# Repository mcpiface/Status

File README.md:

# McPiFace Status Board

Rack Mountable Raspberry Pi Status Board.

A status board in the McPiFace series, intended to fit the 19" rack frame as a quick status indicator.

Based on the Status Board Hat: https://thepihut.com/products/status-board-pro

## Versions

Version 2: Uses MCP23017 with The Pi's I2C. Uses the McPi I2C 6 Pin JST SH connection
https://github.com/mcpiface/Status/tree/master/V2

Version 1: Needs 3x connectors and 15 GPIO on Pi. Uses Pi GPIOs - similar (different pins) to the Status Board Hat.
https://github.com/mcpiface/Status/tree/master/V1

## Sled

To mount the raspberry Pi a 3D printable sled is available:

https://www.thingiverse.com/thing:3488157

## Rack Mount Frame

DAP Audio 2 HE Rackblende f. Modulsystem 10 Segmente MP-1 from Music Store.

* UK: https://www.dv247.com/en_GB/GBP/DAP-Audio-2-HE-Rackblende-f-Modulsystem-10-Segmente-MP-1/art-PAH0017160-000

* Germany: https://www.musicstore.de/en_US/USD/DAP-Audio-2-HE-Rackblende-f-Modulsystem-10-Segmente-MP-1/art-PAH0017160-000

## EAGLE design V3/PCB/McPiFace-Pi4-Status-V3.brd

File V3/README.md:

# McPiFace Status Board - Version 2

Rack Mountable Raspberry Pi Status Board.

Features 4x status indicators with red/green LEDs and optional buttons.

A status board in the McPiFace series, intended to fit the 19" rack frame as a quick status indicator.

This version uses the MCP23017 with The Pi's I2C. 

The connection uses the McPi I2C 6 Pin JST SH connection (1:1 connection with the first 6 pins of the Raspberry Pi second row of pins on the 40 pin header).

![Schematic] (Images/Schematic.png)

## Examples

See the examples folder for examples of use.

## Sled

To mount the raspberry Pi a 3D printable sled is available:

https://www.thingiverse.com/thing:3488157

## Rack Mount Frame

DAP Audio 2 HE Rackblende f. Modulsystem 10 Segmente MP-1 from Music Store.

* UK: https://www.dv247.com/en_GB/GBP/DAP-Audio-2-HE-Rackblende-f-Modulsystem-10-Segmente-MP-1/art-PAH0017160-000

* Germany: https://www.musicstore.de/en_US/USD/DAP-Audio-2-HE-Rackblende-f-Modulsystem-10-Segmente-MP-1/art-PAH0017160-000

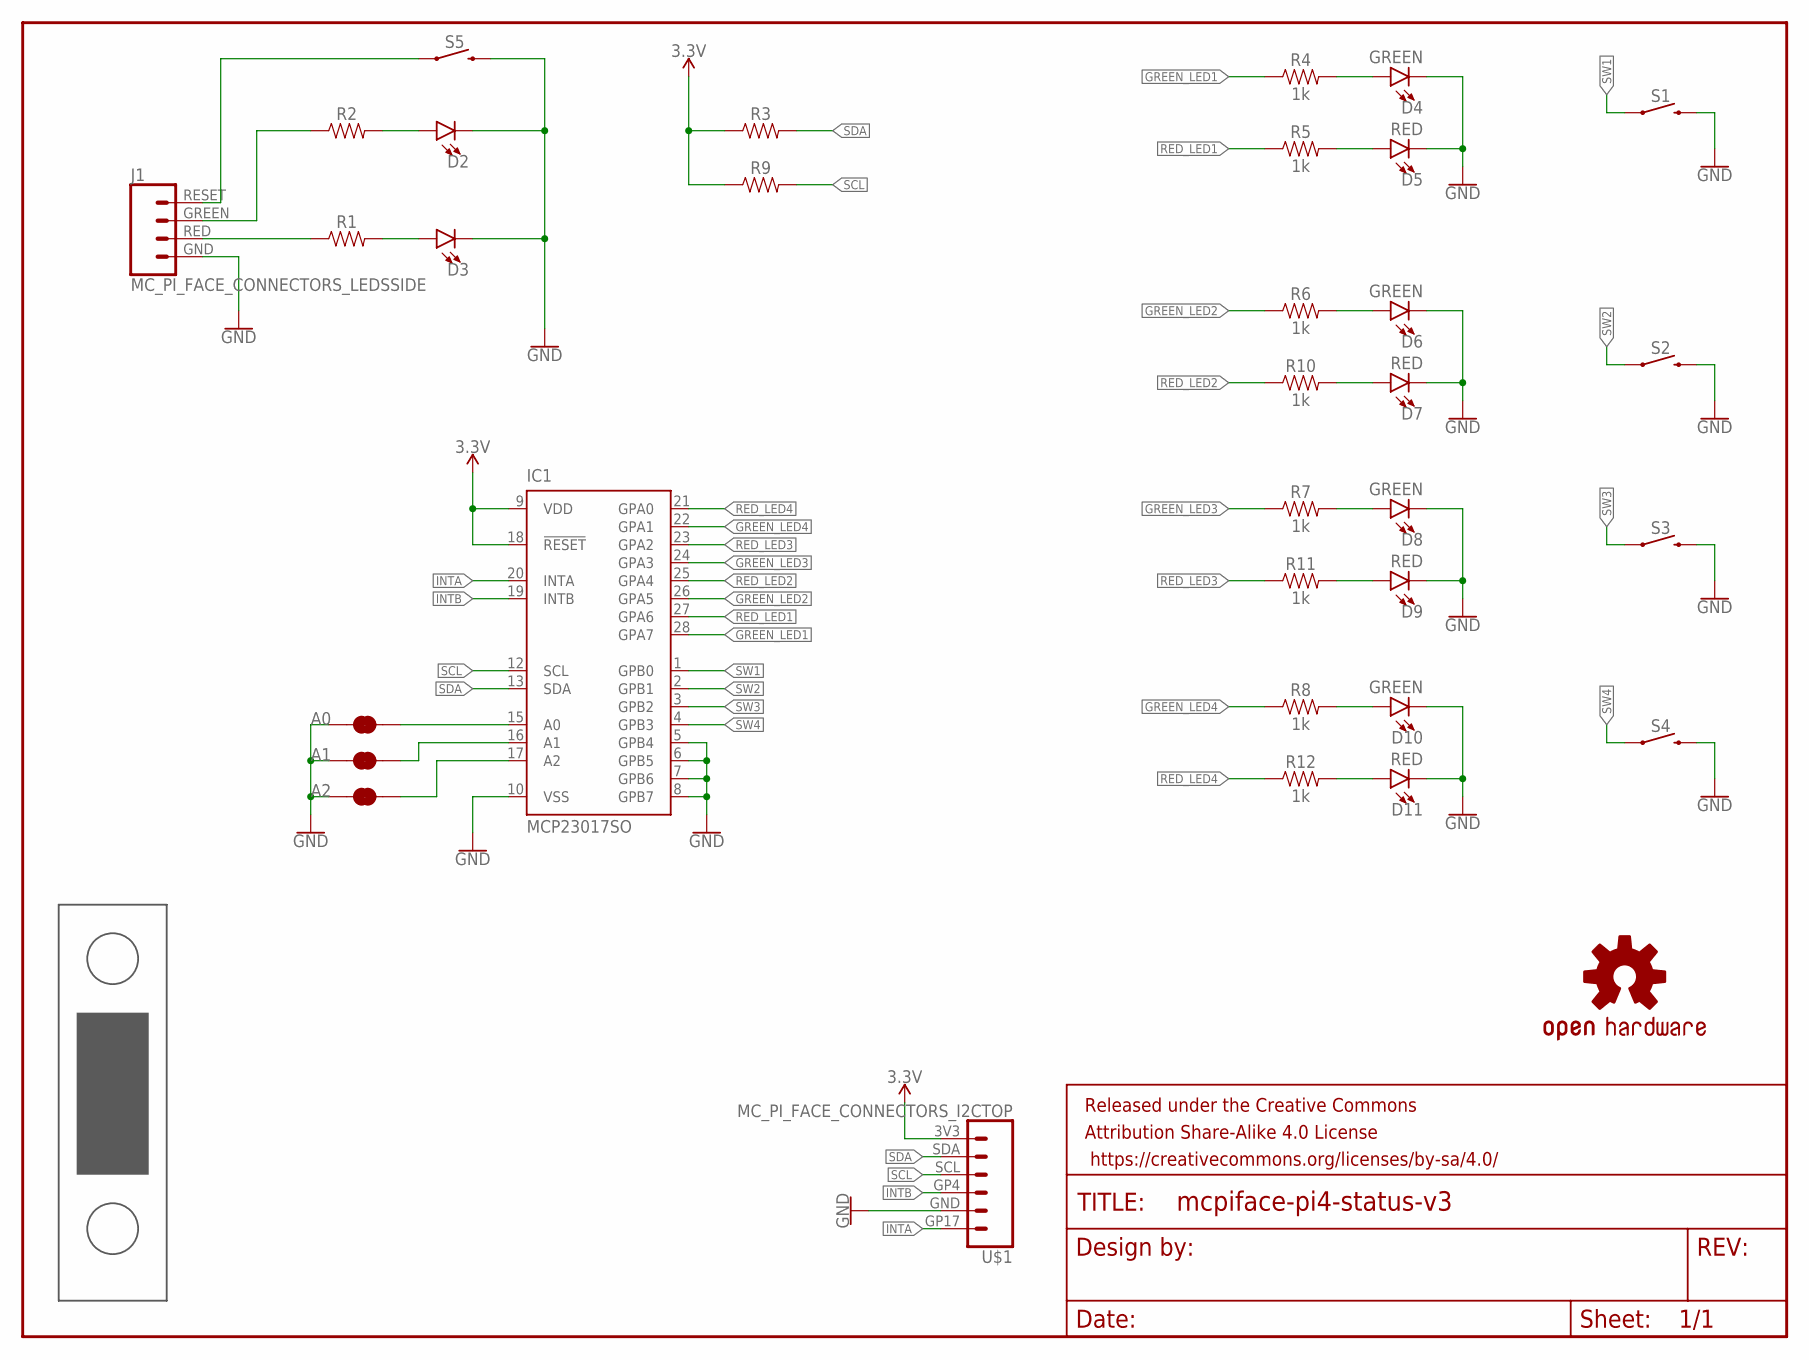
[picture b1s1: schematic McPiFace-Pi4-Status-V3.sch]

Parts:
A0, A1, A2: JUMPER-SMT_2_NC_TRACE_SILK; SMT-JUMPER_2_NC_TRACE_SILK
D2: LEDLED-1206-BOTTOM-2.0MM-GREEN; LED-1206-BOTTOM-2.0MM
D3: LEDLED-1206-BOTTOM-2.0MM-RED; LED-1206-BOTTOM-2.0MM
D4, D6, D8, D10: GREEN; LED-1206-BOTTOM-2.0MM
D5, D7, D9, D11: RED; LED-1206-BOTTOM-2.0MM
FP1: MC_PI_4_FACE_PANELDOUBLE; MC_PI_4-DOUBLE_FACE
FRAME1: FRAME-LETTER; CREATIVE_COMMONS
IC1: MCP23017SO; SO28W
J1: MC_PI_FACE_CONNECTORS_LEDSSIDE; JST-4-SH-1.0MM-SIDE
LOGO1: OSHW-LOGOL; OSHW-LOGO-L
R1, R2, R3, R9: 0805
R4, R5, R6, R7, R8, R10, R11, R12: 1k; 0805
S1, S5: MOMENTARY-SWITCH-SPSTTACKTILE_SWITCH_PTH_6.0MM_NO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; TACTILE_SWITCH_PTH_6.0MM_NO_TOP_RESIST; FARNELL 2435162
S2, S3, S4: MOMENTARY-SWITCH-SPSTTACKTILE_SWITCH_PTH_6.0MM_NO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; TACTILE_SWITCH_PTH_6.0MM_NO_TOP_RESIST
U$1: MC_PI_FACE_CONNECTORS_I2CTOP; JST-6-SH-1.0MM-TOP

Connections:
3.3V: IC1.9 (VDD), IC1.18 (!RESET), R3.1, R9.1, U$1.3V3
GND: A0.1, A1.1, A2.1, D2.C, D3.C, D4.C, D5.C, D6.C, D7.C, D8.C, D9.C, D10.C, D11.C, IC1.5 (GPB4), IC1.6 (GPB5), IC1.7 (GPB6), IC1.8 (GPB7), IC1.10 (VSS), J1.GND, S1.3 (2), S2.3 (2), S3.3 (2), S4.3 (2), S5.3 (2), U$1.GND
GREEN_LED1: IC1.28 (GPA7), R4.1
GREEN_LED2: IC1.26 (GPA5), R6.1
GREEN_LED3: IC1.24 (GPA3), R7.1
GREEN_LED4: IC1.22 (GPA1), R8.1
INTA: IC1.20 (INTA), U$1.GP17
INTB: IC1.19 (INTB), U$1.GP4
unnamed: D4.A, R4.2
unnamed: J1.RESET, S5.1
unnamed: D2.A, R2.2
unnamed: D3.A, R1.2
unnamed: J1.RED, R1.1
unnamed: J1.GREEN, R2.1
unnamed: D6.A, R6.2
unnamed: D10.A, R8.2
unnamed: D8.A, R7.2
unnamed: D5.A, R5.2
unnamed: D7.A, R10.2
unnamed: D9.A, R11.2
unnamed: D11.A, R12.2
unnamed: A0.2, IC1.15 (A0)
unnamed: A1.2, IC1.16 (A1)
unnamed: A2.2, IC1.17 (A2)
RED_LED1: IC1.27 (GPA6), R5.1
RED_LED2: IC1.25 (GPA4), R10.1
RED_LED3: IC1.23 (GPA2), R11.1
RED_LED4: IC1.21 (GPA0), R12.1
SCL: IC1.12 (SCL), R9.2, U$1.SCL
SDA: IC1.13 (SDA), R3.2, U$1.SDA
SW1: IC1.1 (GPB0), S1.1
SW2: IC1.2 (GPB1), S2.1
SW3: IC1.3 (GPB2), S3.1
SW4: IC1.4 (GPB3), S4.1

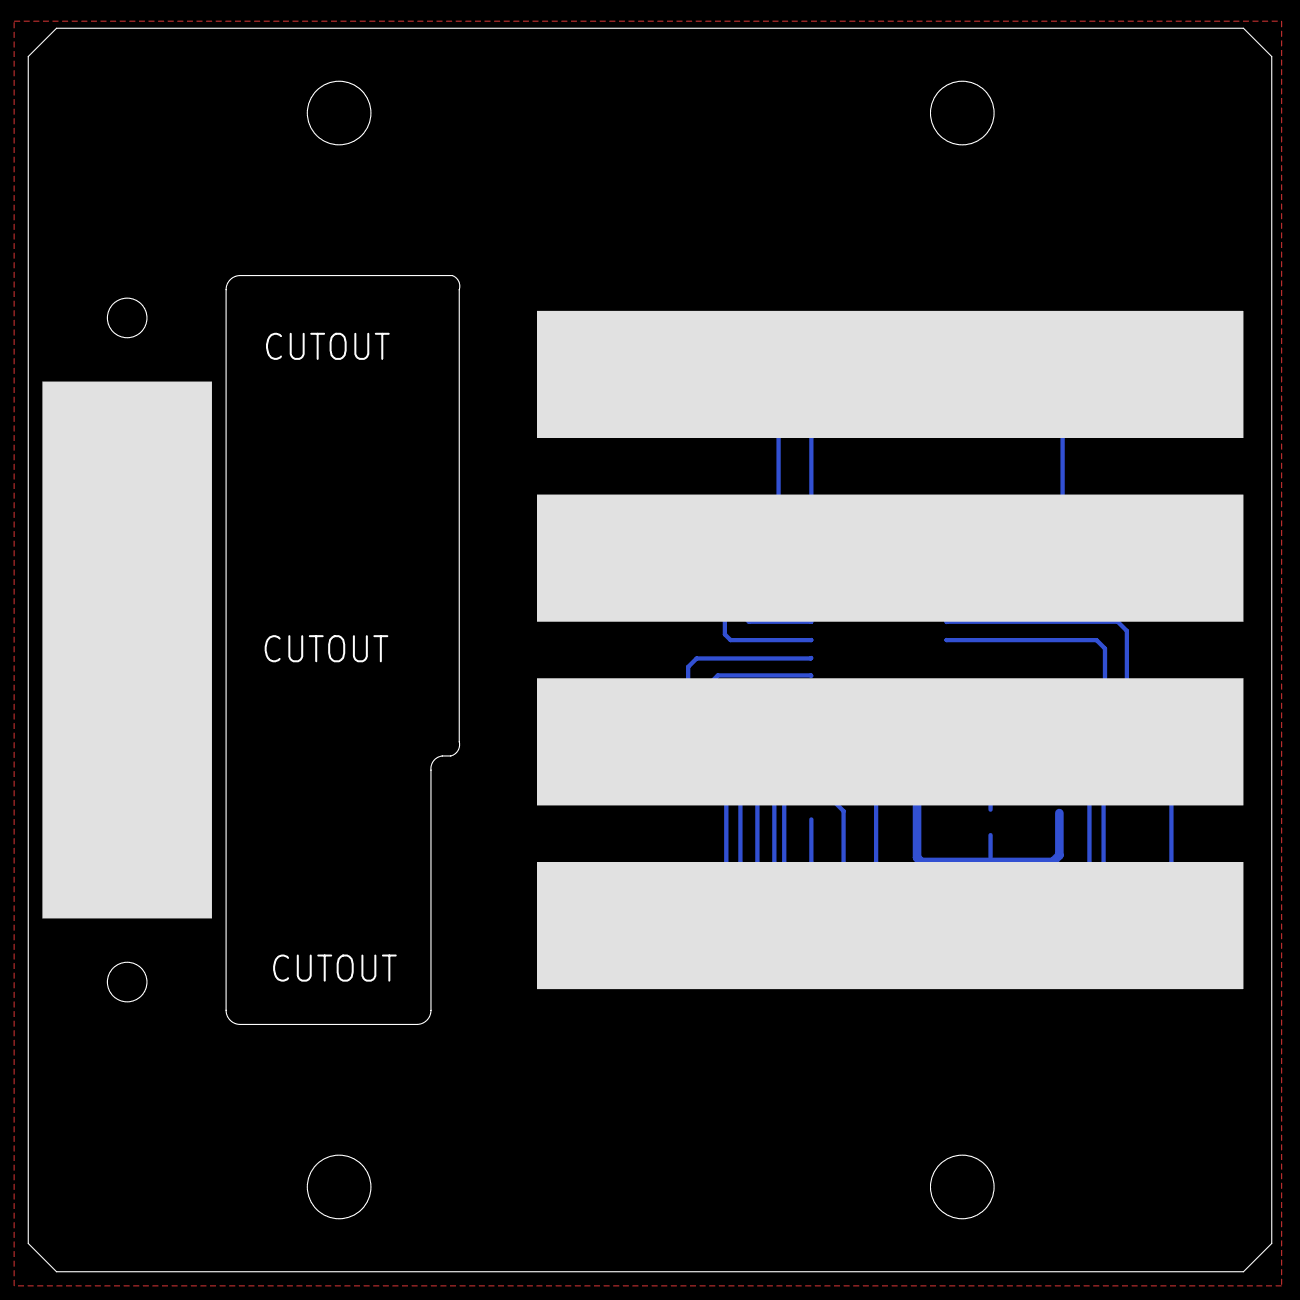
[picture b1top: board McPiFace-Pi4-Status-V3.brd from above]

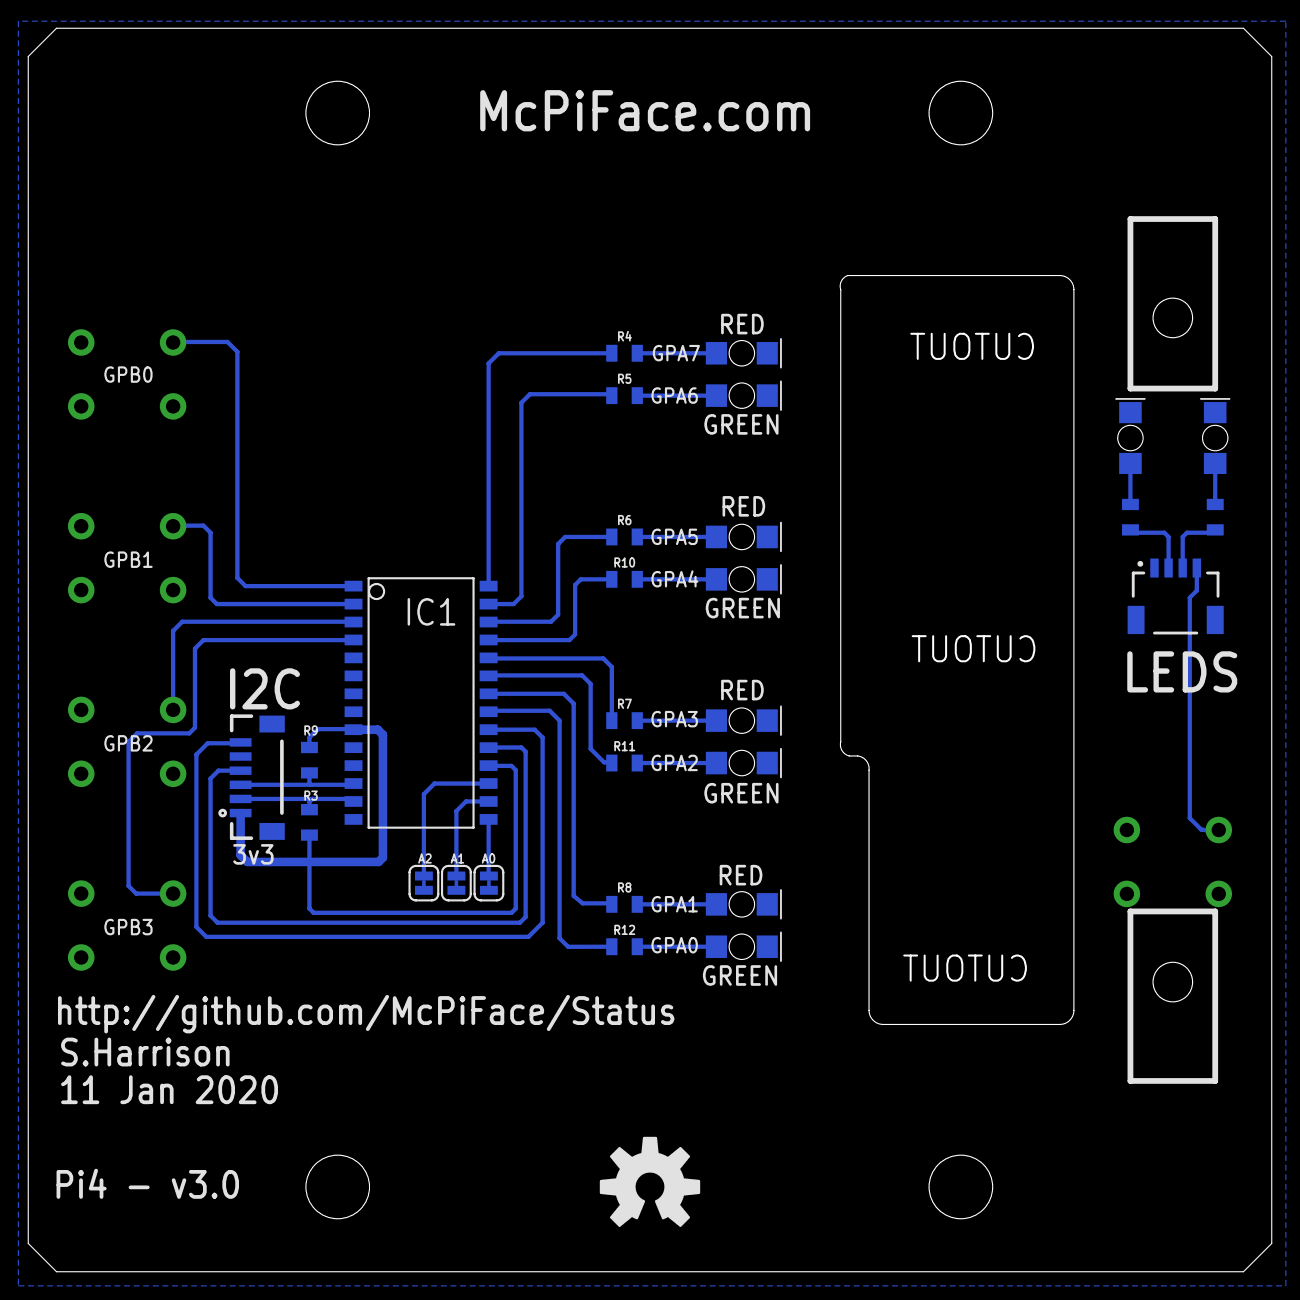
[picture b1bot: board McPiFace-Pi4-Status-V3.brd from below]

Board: 2 copper layers, 88.0 x 88.0 mm, 36 parts (29 on the bottom side), 34 nets.

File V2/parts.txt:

Partlist

Exported from McPiFace-Status-V2.brd at 16/02/2019 17:04

EAGLE Version 7.4.0 Copyright (c) 1988-2015 CadSoft

Assembly variant: 

Part     Value                                                        Package                                Library            Position (mm)         Orientation

A0       JUMPER-SMT_2_NC_TRACE_SILK                                   SMT-JUMPER_2_NC_TRACE_SILK             SparkFun-Jumpers   (55.4 27.5)           MR90
A1       JUMPER-SMT_2_NC_TRACE_SILK                                   SMT-JUMPER_2_NC_TRACE_SILK             SparkFun-Jumpers   (57.7 27.5)           MR90
A2       JUMPER-SMT_2_NC_TRACE_SILK                                   SMT-JUMPER_2_NC_TRACE_SILK             SparkFun-Jumpers   (60 27.5)             MR90
D2                                                                    LED-1206-BOTTOM-2.0MM                  ThingySticks       (4 59)                MR90
D3                                                                    LED-1206-BOTTOM-2.0MM                  ThingySticks       (10 59)               MR90
D4       GREEN                                                        LED-1206-BOTTOM-2.0MM                  ThingySticks       (37.5 65)             MR0
D5       RED                                                          LED-1206-BOTTOM-2.0MM                  ThingySticks       (37.5 62)             MR0
D6       GREEN                                                        LED-1206-BOTTOM-2.0MM                  ThingySticks       (37.5 52)             MR0
D7       RED                                                          LED-1206-BOTTOM-2.0MM                  ThingySticks       (37.5 49)             MR0
D8       GREEN                                                        LED-1206-BOTTOM-2.0MM                  ThingySticks       (37.5 39)             MR0
D9       RED                                                          LED-1206-BOTTOM-2.0MM                  ThingySticks       (37.5 36)             MR0
D10      GREEN                                                        LED-1206-BOTTOM-2.0MM                  ThingySticks       (37.5 26)             MR0
D11      RED                                                          LED-1206-BOTTOM-2.0MM                  ThingySticks       (37.5 23)             MR0
IC1      MCP23017SO                                                   SO28W                                  McPiFace           (60.2 40.9)           MR270
J1       MC_PI_FACE_CONNECTORS_LEDSSIDE                               JST-4-SH-1.0MM-SIDE                    McPiFace           (6.8 49.8)            MR0
R1                                                                    0805                                   SparkFun-Resistors (10 53.4)             MR90
R2                                                                    0805                                   SparkFun-Resistors (4 53.4)              MR90
R3                                                                    0805                                   SparkFun-Resistors (68.1 31.8)           MR90
R4       1k                                                           0805                                   SparkFun-Resistors (45.8 65)             MR0
R5       1k                                                           0805                                   SparkFun-Resistors (45.8 62)             MR0
R6       1k                                                           0805                                   SparkFun-Resistors (45.8 52)             MR0
R7       1k                                                           0805                                   SparkFun-Resistors (45.8 39)             MR0
R8       1k                                                           0805                                   SparkFun-Resistors (45.8 26)             MR0
R9                                                                    0805                                   SparkFun-Resistors (68.1 36.2)           MR270
R10      1k                                                           0805                                   SparkFun-Resistors (45.8 49)             MR0
R11      1k                                                           0805                                   SparkFun-Resistors (45.8 36)             MR0
R12      1k                                                           0805                                   SparkFun-Resistors (45.8 23)             MR0
S1       MOMENTARY-SWITCH-SPSTTACKTILE_SWITCH_PTH_6.0MM_NO_TOP_RESIST TACTILE_SWITCH_PTH_6.0MM_NO_TOP_RESIST ThingySticks       (81 63.5)             R0
S2       MOMENTARY-SWITCH-SPSTTACKTILE_SWITCH_PTH_6.0MM_NO_TOP_RESIST TACTILE_SWITCH_PTH_6.0MM_NO_TOP_RESIST ThingySticks       (81 50.5)             R0
S3       MOMENTARY-SWITCH-SPSTTACKTILE_SWITCH_PTH_6.0MM_NO_TOP_RESIST TACTILE_SWITCH_PTH_6.0MM_NO_TOP_RESIST ThingySticks       (81 37.5)             R0
S4       MOMENTARY-SWITCH-SPSTTACKTILE_SWITCH_PTH_6.0MM_NO_TOP_RESIST TACTILE_SWITCH_PTH_6.0MM_NO_TOP_RESIST ThingySticks       (81 24.5)             R0
S5       MOMENTARY-SWITCH-SPSTTACKTILE_SWITCH_PTH_6.0MM_NO_TOP_RESIST TACTILE_SWITCH_PTH_6.0MM_NO_TOP_RESIST ThingySticks       (7 29)                R0
U$1      MC_PI_FACE_CONNECTORS_I2CTOP                                 JST-6-SH-1.0MM-TOP                     McPiFace           (71.7 35)             MR90

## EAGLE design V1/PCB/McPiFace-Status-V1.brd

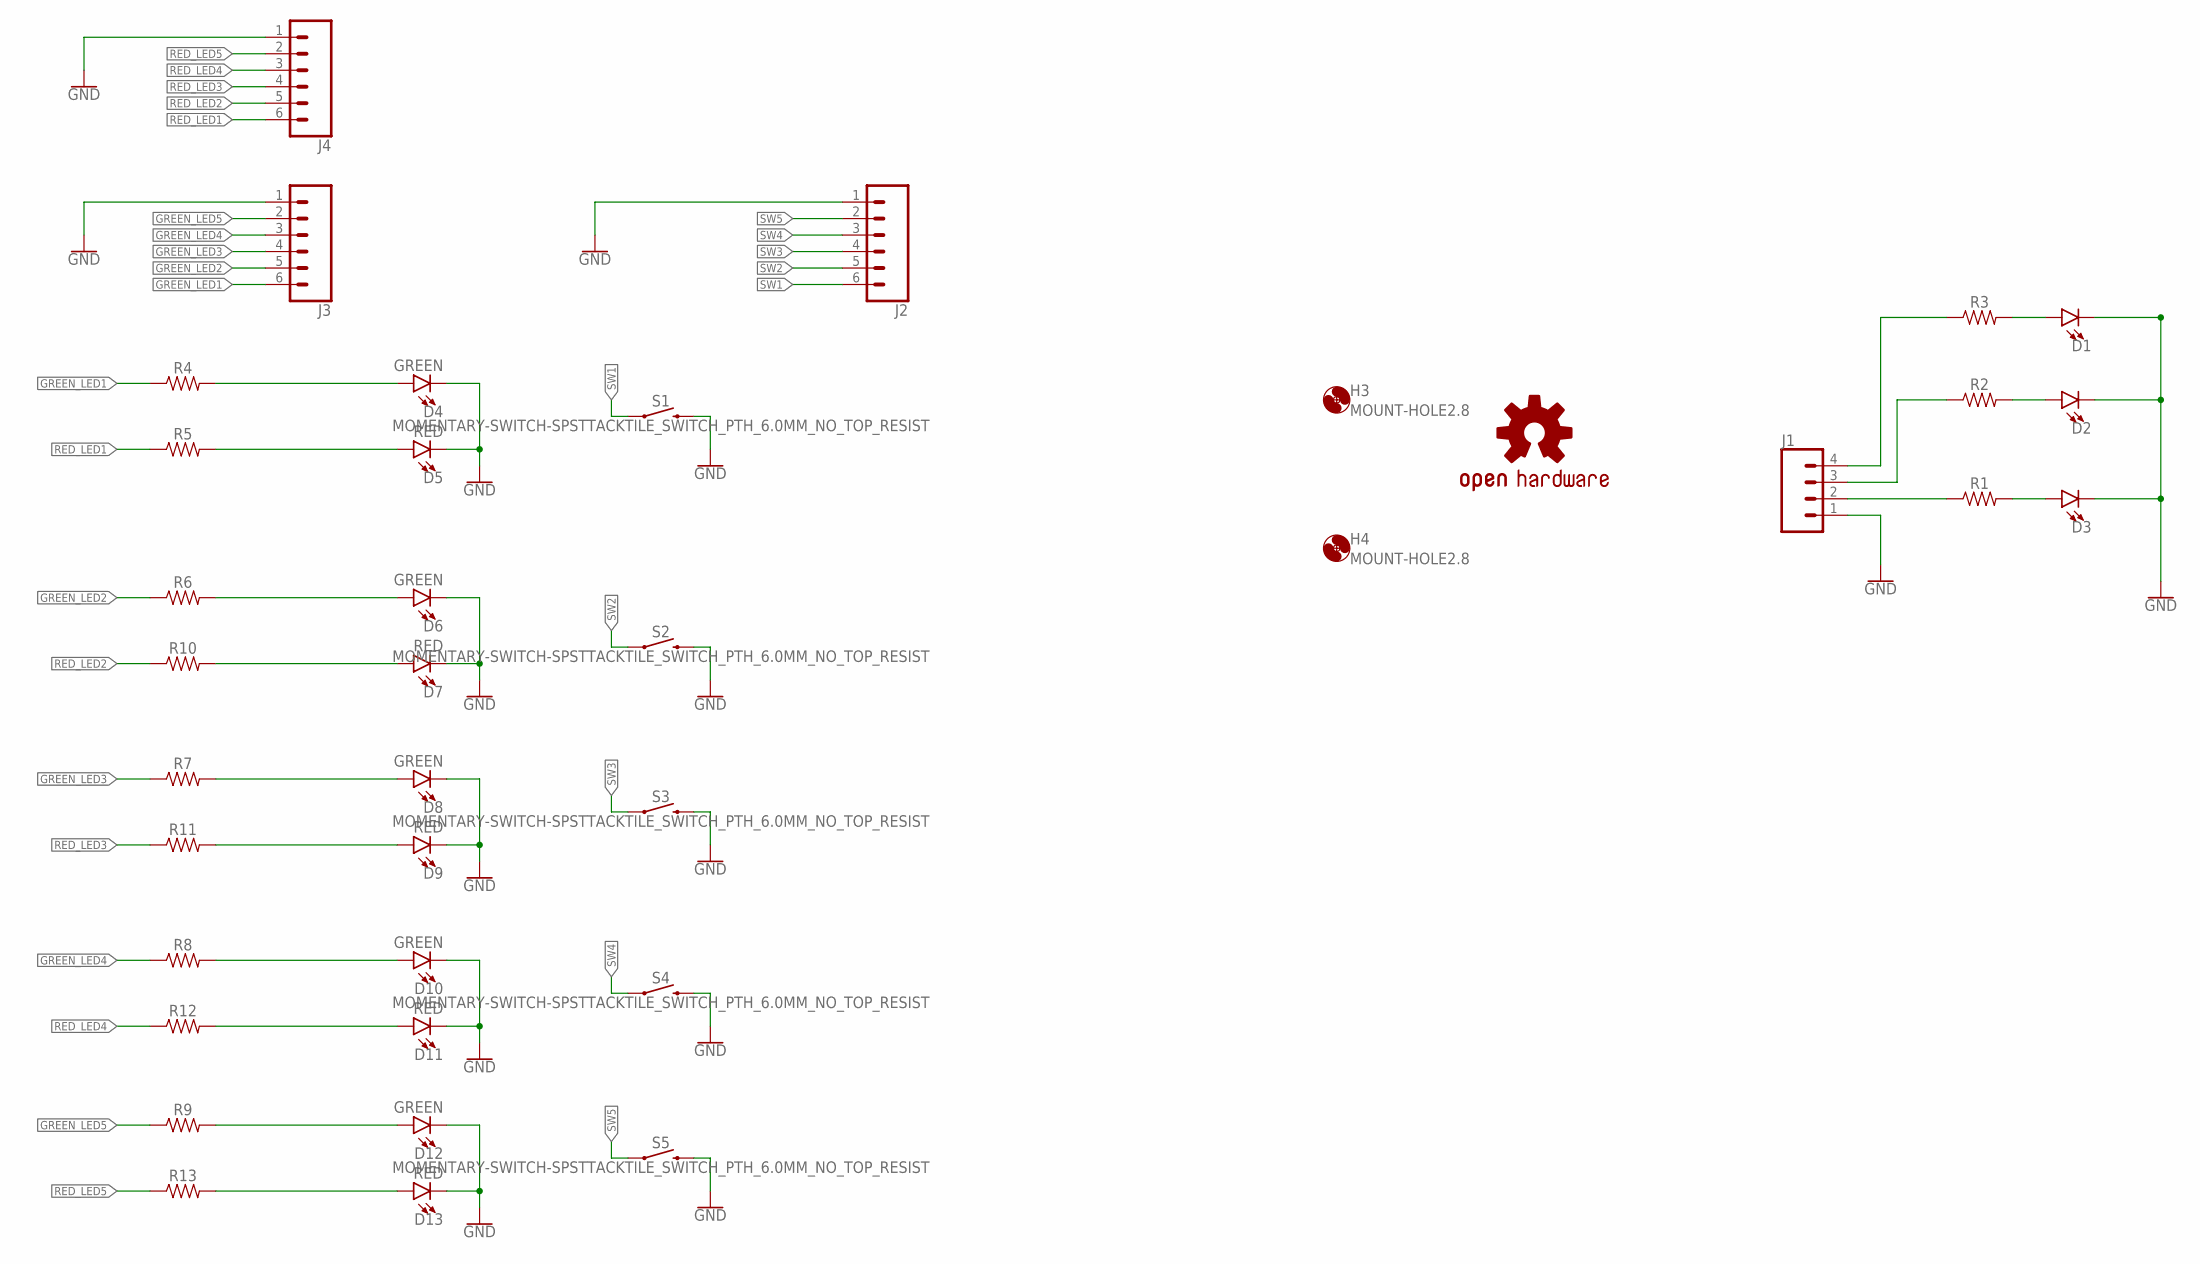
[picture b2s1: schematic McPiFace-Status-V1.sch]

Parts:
D1, D2, D3: LED1206-BOTTOM-1.6MM; LED-1206-BOTTOM-1.6MM
D4, D6, D8, D10, D12: GREEN; LED-1206
D5, D7, D9, D11, D13: RED; LED-1206
H3, H4: MOUNT-HOLE2.8; 2,8
J1: CONN_04SMD2; 1X04_1MM_RA
J2, J3, J4: CONN_06SMD-1MM; 1X06-1MM
LOGO1: OSHW-LOGOL; OSHW-LOGO-L
R1, R2, R3: 1206
R4, R5, R6, R7, R8, R9, R10, R11, R12, R13: 0805
S1: MOMENTARY-SWITCH-SPSTTACKTILE_SWITCH_PTH_6.0MM_NO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; TACTILE_SWITCH_PTH_6.0MM_NO_TOP_RESIST; FARNELL 2435162
S2, S3, S4, S5: MOMENTARY-SWITCH-SPSTTACKTILE_SWITCH_PTH_6.0MM_NO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; TACTILE_SWITCH_PTH_6.0MM_NO_TOP_RESIST

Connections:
GND: D1.C, D2.C, D3.C, D4.C, D5.C, D6.C, D7.C, D8.C, D9.C, D10.C, D11.C, D12.C, D13.C, J1.1, J2.1, J3.1, J4.1, S1.3 (2), S2.3 (2), S3.3 (2), S4.3 (2), S5.3 (2)
GREEN_LED1: J3.6, R4.1
GREEN_LED2: J3.5, R6.1
GREEN_LED3: J3.4, R7.1
GREEN_LED4: J3.3, R8.1
GREEN_LED5: J3.2, R9.1
unnamed: D4.A, R4.2
unnamed: D1.A, R3.2
unnamed: D2.A, R2.2
unnamed: D3.A, R1.2
unnamed: J1.2, R1.1
unnamed: J1.3, R2.1
unnamed: J1.4, R3.1
unnamed: D6.A, R6.2
unnamed: D12.A, R9.2
unnamed: D10.A, R8.2
unnamed: D8.A, R7.2
unnamed: D5.A, R5.2
unnamed: D7.A, R10.2
unnamed: D9.A, R11.2
unnamed: D11.A, R12.2
unnamed: D13.A, R13.2
RED_LED1: J4.6, R5.1
RED_LED2: J4.5, R10.1
RED_LED3: J4.4, R11.1
RED_LED4: J4.3, R12.1
RED_LED5: J4.2, R13.1
SW1: J2.6, S1.1
SW2: J2.5, S2.1
SW3: J2.4, S3.1
SW4: J2.3, S4.1
SW5: J2.2, S5.1

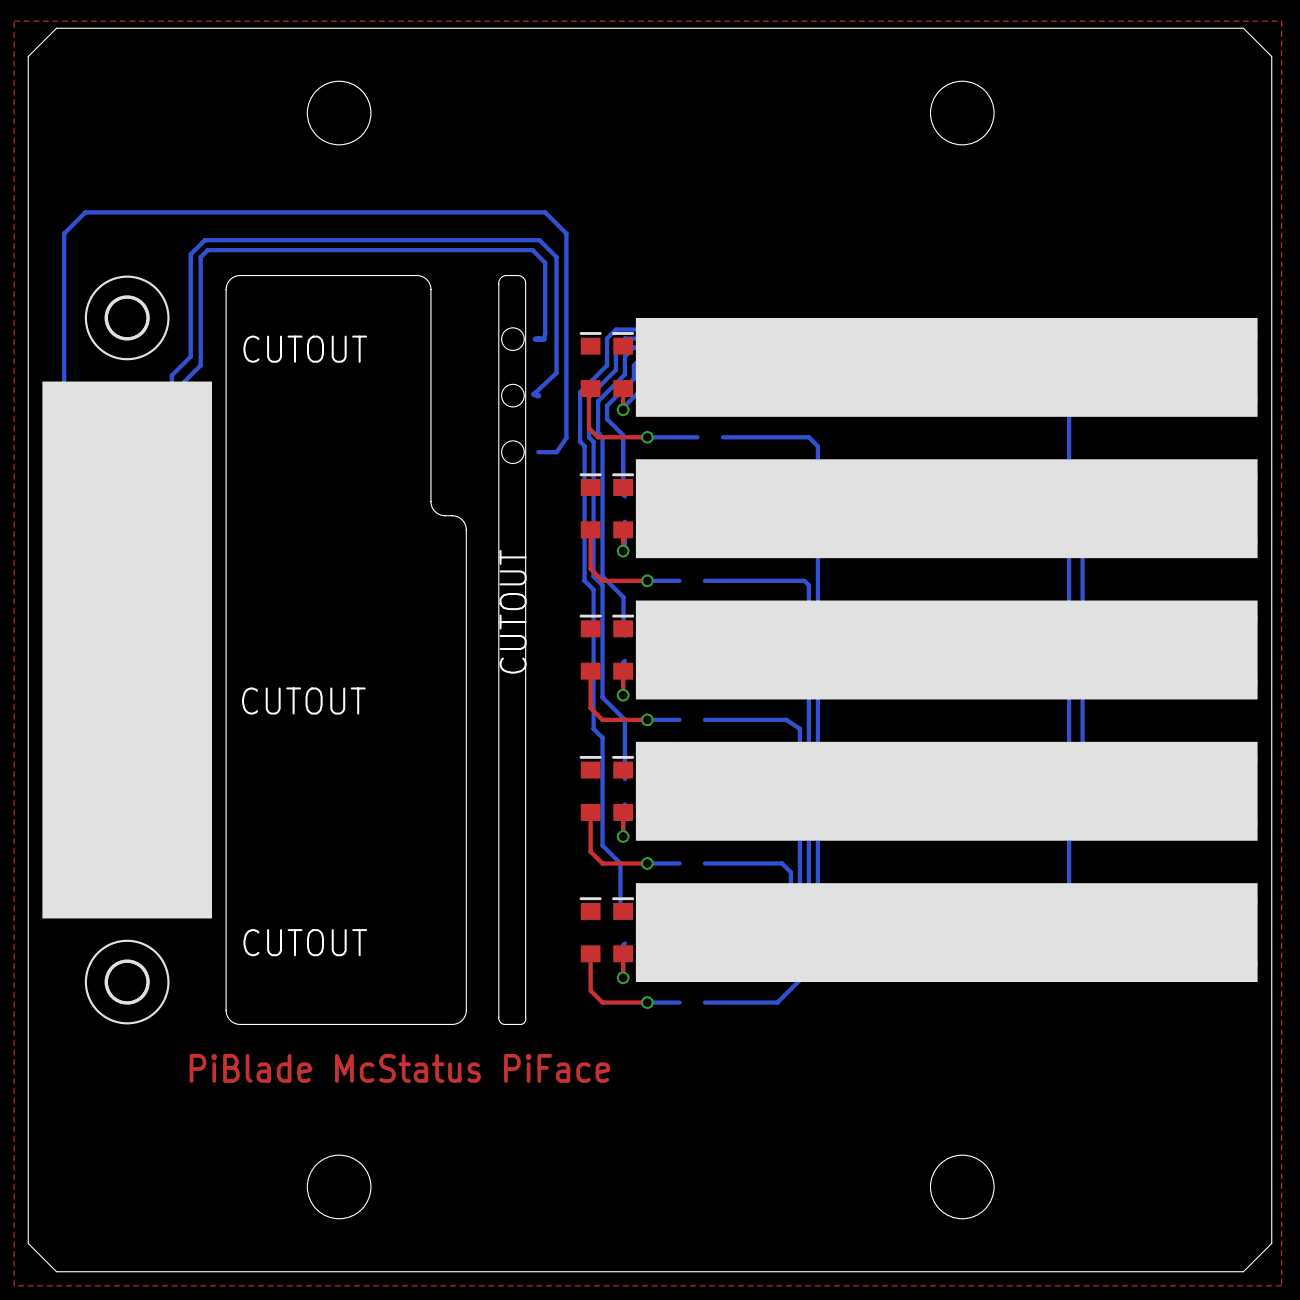
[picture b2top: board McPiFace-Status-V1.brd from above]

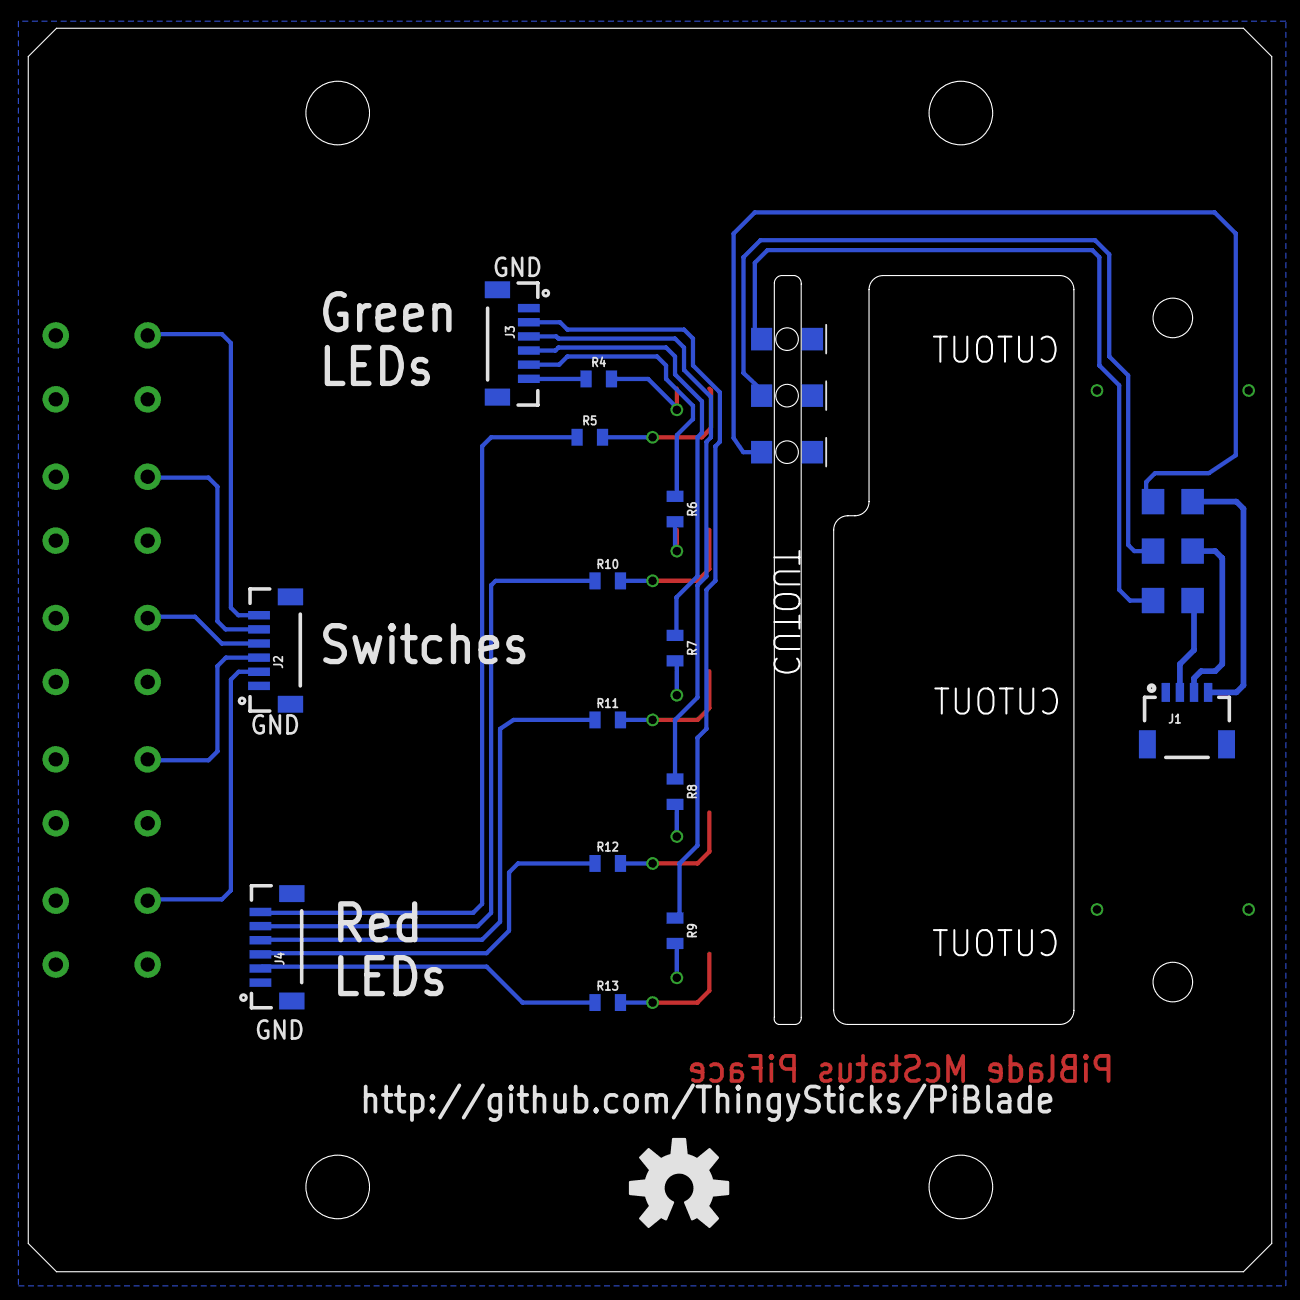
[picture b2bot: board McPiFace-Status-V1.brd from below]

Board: 2 copper layers, 88.0 x 88.0 mm, 38 parts (21 on the bottom side), 32 nets.

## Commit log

2019-02-09 Copied V1 over from ThingySticks respository.
    Added V2 to use I2C interface with IO driver chip and 2 interrupt options.
2019-03-12 Updated main readme and added image and example for V2
2019-03-12 Updated LEDs used to use the larger hole version.
2019-03-13 Changed to use a smaller size file for the example
2019-03-13 Added V2 readme and images.
2019-03-13 Improved readme, hopefully fixing the image link....
2019-03-13 Updated images and general text for readme.
2019-03-13 Maybe I'll get the image links right this time.
2019-03-13 Nearly. Fixing another image link
2020-12-16 Fix I2C wiring image.
2020-12-16 Added V3

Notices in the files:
parts and their libraries:
SparkFun-Aesthetics: Licensing: Creative Commons ShareAlike 4.0 International - https://creativecommons.org/licenses/by-sa/4.0
SparkFun-Aesthetics: Released under the Creative Commons Attribution Share-Alike 4.0 License
SparkFun-Aesthetics: https://creativecommons.org/licenses/by-sa/4.0
